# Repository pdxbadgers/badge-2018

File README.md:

# badge-2018  
BSidesPDX 2018 badge

## Art  
image resouce files

## FW  
C source code

## HW  
KiCad soruce files, BOM, datasheets

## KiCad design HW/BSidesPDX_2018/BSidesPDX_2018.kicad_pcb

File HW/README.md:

## Resources
passive compoenent footprints: https://github.com/esden/pretty-kicad-libs  
SAO symbol and footprint: https://hackaday.io/project/52950-defcon-26-shitty-add-ons
DigiKey symbols and footprints: https://www.digikey.com/en/resources/design-tools/kicad

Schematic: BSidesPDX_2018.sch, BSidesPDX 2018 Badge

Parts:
BT1: Battery_Cell; CR2030_Retainer
C1: 10u; C_0805
C2: 0.1u; C_0603
D1, D2, D3, D4, D5, D6, D7, D8, D9, D10, D11, D12: YLW_LED; OSRAM_LED
D13, D14: D_Zener; D_SOD-323
D101, D102, D103, D104: RGB_LED
J1: AVR-ISP-6; AVR_ISP_2x3_P2.54mm_SMD
J2: USB_B_Micro
R1, R2, R3, R4, R101, R102, R103, R104: 100R; C_0603
R5, R6: 68R; C_0603
R7: 1K5; C_0603
S1, S2: PTS645SM43SMTR92_LFS; Switch_Tactile_SMD_6x6mm_PTS645; MPN PTS645SM43SMTR92 LFS; Digi-Key_PN CKN9112CT-ND
U1: ATTINY861-15XD; TSSOP-20_4.4x6.5mm_P0.65mm
X1, X2, X3, X4: Badgelife_shitty_connector; PRESS_FIT_SAO_CNX

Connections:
/3V0: BT1.1, C1.1, C2.1, J1.2, J2.1, R7.1, U1.5 (VCC), U1.15 (AVCC), X1.1, X2.1, X3.1, X4.1
/B_PWM__D+: D101.4, D102.4, D103.4, D104.4, R5.1, U1.8 (XTAL2/PB5)
/D+: D13.1, J2.3, R5.2
/D-: D14.1, J2.2, R6.1, R7.2
/EN_RGB1: R101.1, U1.14 (PA4)
/EN_RGB2: R102.1, U1.13 (PA5)
/EN_RGB3: R103.1, U1.12 (PA6)
/EN_RGB4: R104.1, U1.11 (PA7)
/G_PWM: D101.3, D102.3, D103.3, D104.3, U1.4 (PB3)
/L_SWITCH_D-: R6.2, S1.1, S1.2, U1.7 (XTAL1/PB4)
/NC: J2.4
/ROW1: R1.1, U1.20 (PA0)
/ROW2: R2.1, U1.19 (PA1)
/ROW3: R3.1, U1.18 (PA2)
/ROW4: R4.1, U1.17 (AREF/PA3)
/ROW_1: D1.2, D2.2, D3.2, D4.1, D7.1, D8.1, R1.2
/ROW_2: D1.1, D4.2, D5.2, D6.2, D9.1, D10.1, R2.2
/ROW_3: D2.1, D5.1, D8.2, D10.2, D11.1, D12.2, R3.2
/ROW_4: D3.1, D6.1, D7.2, D9.2, D11.2, D12.1, R4.2
/R_PWM__MISO: D101.1, D102.1, D103.1, D104.1, J1.1, U1.2 (PB1)
/R_SWITCH: S2.1, S2.2, U1.9 (PB6)
/SCL_SCK: J1.3, U1.3 (PB2), X1.3, X2.3, X3.3, X4.3
/SDA_MOSI: J1.4, U1.1 (PB0), X1.4, X2.4, X3.4, X4.4
/~RESET: J1.5, U1.10 (~RESET~/PB7)
GND: BT1.2, C1.2, C2.2, D13.2, D14.2, J1.6, J2.5, J2.6, S1.3, S1.4, S2.3, S2.4, U1.6 (GND), U1.16 (AGND), X1.2, X2.2, X3.2, X4.2
unnamed: D101.2, R101.2
unnamed: D102.2, R102.2
unnamed: D103.2, R103.2
unnamed: D104.2, R104.2

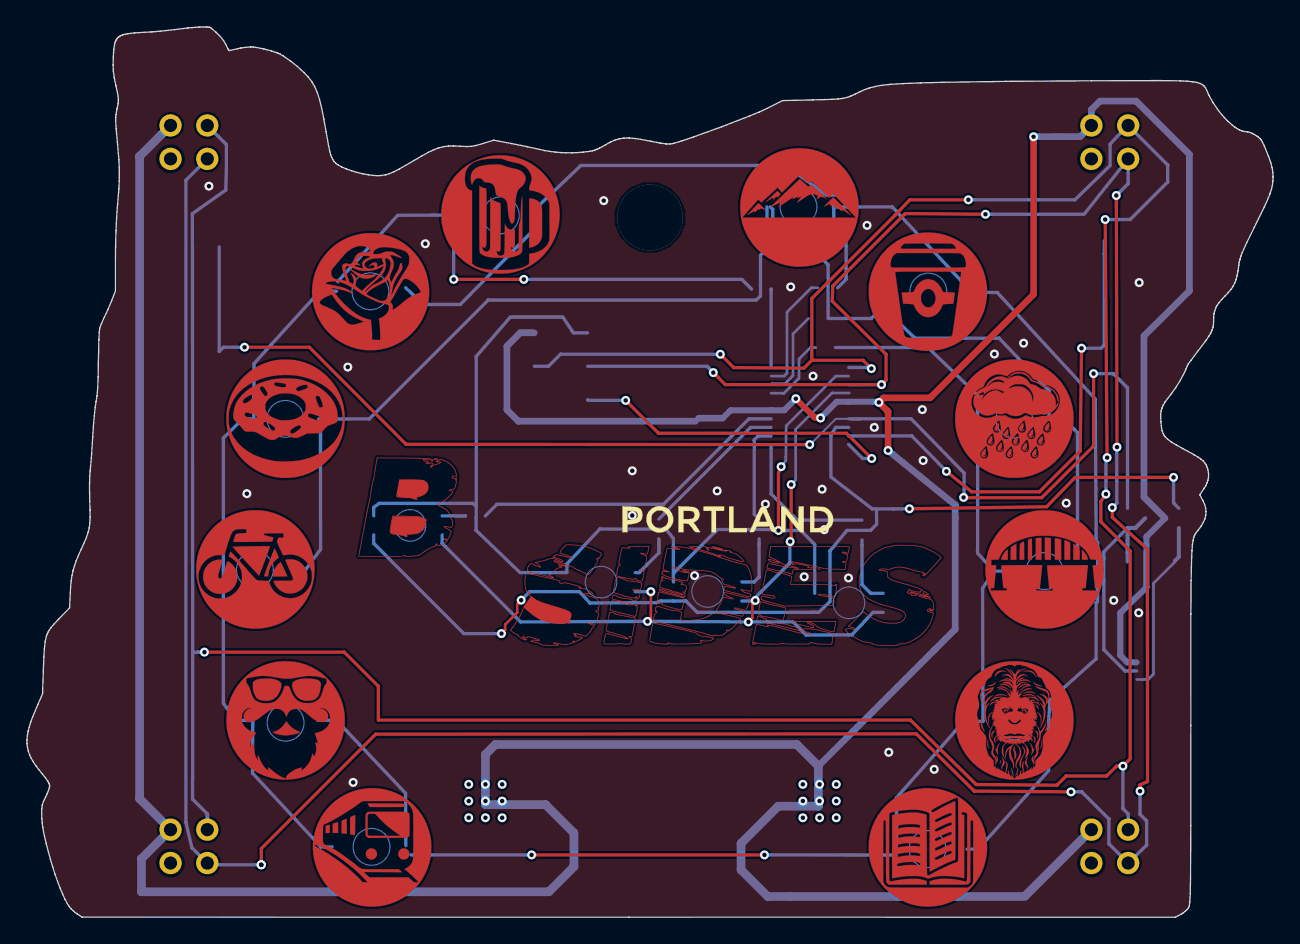
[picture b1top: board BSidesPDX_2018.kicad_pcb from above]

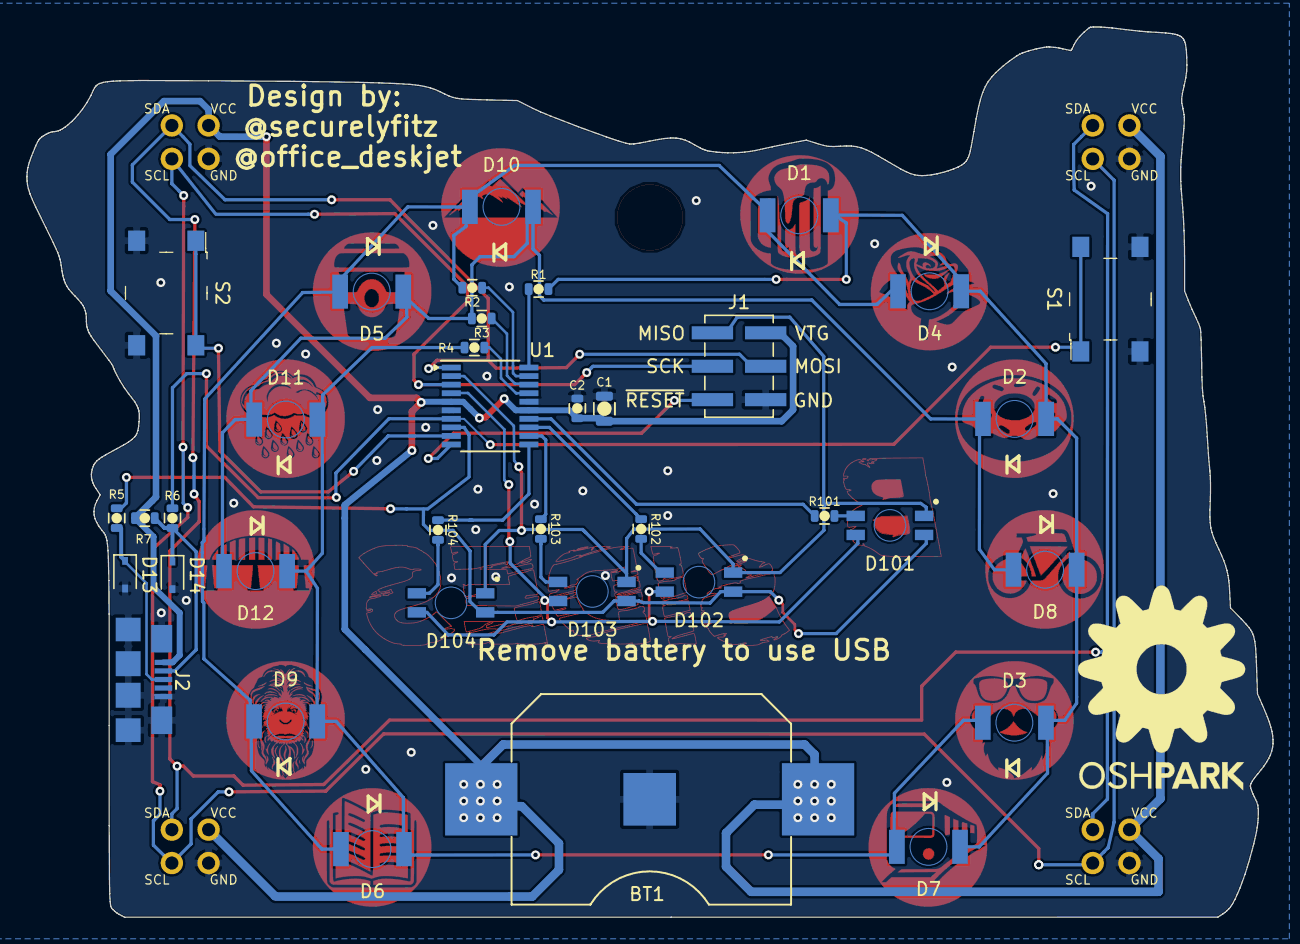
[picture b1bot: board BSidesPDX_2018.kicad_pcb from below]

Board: 2 copper layers, 94.7 x 67.7 mm, 44 parts (21 on the bottom side), 28 nets.

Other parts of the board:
ART_Cu: LOGO; F_Cu
MASK_ART: LOGO; F_Mask
PDX: LOGO; F_Silk

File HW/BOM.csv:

Description,Designator,Packing,Value,QTY/Board,Manufacturer Part #,Supplier Part #,Supplier Link,Comment,Packaging,Order Quantity,Order Cost
RGB LED,D101-D104,Gull Wing 4pin,RGB_LED,4,XZMDKCBDDG45S-9 ,1497-1257-2-ND,https://www.digikey.com/product-detail/en/sunled/XZMDKCBDDG4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,,Tape & Reel,2000,$859.18
Yellow LED,D1-D12,Gull Wing 2pin,YLW_LED,12,LY T776-S1T1-26-Z ,475-2801-2-ND ,https://www.digikey.com/product-detail/en/osram-opto-semicon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,,Tape & Reel,6000,$744.21
Zener Diodes,D13 D14,SOD323,D_Zener,2, MM3Z3V6T1G ,MM3Z3V6T1GOSDKR-ND ,https://www.digikey.com/product-detail/en/on-semiconductor/M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,,Digi-Reel,1000,$39.45
Resistors,R1-R4 R101-R104,SMD 0603,100R,8, CRGCQ0603J100R ,A130085TR-ND ,https://www.digikey.com/product-detail/en/te-connectivity-pa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,or similar replacement,Tape & Reel,5000,$12.64
Resistors,R5 R6,SMD 0603,68R,2,CR0603-JW-680ELF,CR0603-JW-680ELFTR-ND,https://www.digikey.com/product-detail/en/bourns-inc/CR0603-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,or similar replacement,Tape & Reel,5000,$9.41
Resistors,R7,SMD 0603,1K5,1, CRGCQ0603J1K5 ,A130092TR-ND,https://www.digikey.com/product-detail/en/te-connectivity-pa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,or similar replacement,Tape & Reel,5000,$12.64
Bypass Cap,C1,SMD 0805,10uF,1, CL21A106KPCLQNC , 1276-2402-6-ND ,https://www.digikey.com/product-detail/en/samsung-electro-me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,or similar replacement,Digi-Reel,500,$34.76
Bypass Cap,C2,SMD 0603,0.1uF,1,CL10F104ZB8NNNC,1276-1012-6-ND,https://www.digikey.com/product-detail/en/samsung-electro-me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,or similar replacement,Digi-Reel,500,$13.04
Battery Retainer,BT1,SMD 2pin,Battery_Cell,1,3034TR,36-3034TR-ND,https://www.digikey.com/product-detail/en/keystone-electroni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,,Tape & Reel,500,$156.75
MCU,U1,SOIC 20pin,ATTINY861-15XD ,1,ATTINY861A-XUR ,ATTINY861A-XURDKR-ND ,https://www.digikey.com/product-detail/en/microchip-technolo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,,Digi-Reel,500,$583.80
Switch,SW1 SW2,Gull Wing 4pin,PTS645SM43SMTR92_LFS,2,PTS645SM43SMTR92 LFS ,CKN9112TR-ND,https://www.digikey.com/product-detail/en/c-k/PTS645SM43SMTR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,,Tape & Reel,1000,$99.06
Connector,J2,SMD,USB_B_Micro,1,10118192-0001LF ,609-4613-6-ND ,https://www.digikey.com/product-detail/en/amphenol-fci/10118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,,Digi-Reel,500,$138.01
lanyard,N/A,N/A,N/A,1,N/A,N/A,TBD,,Bulk Bag,,
battery,N/A,CR2032,3V,1,N/A,N/A,ebay.com/itm/1000-X-CR2032-2032-DL2032-LM2032-BR2032-Ultra-Power-bulk-3V-lithium-battery-/222282215964,,Bulk Tray,,
,,,,,,,,,,,"$2,702.95"
,,,,,,,,,,,
MCU,U1,SOIC 20pin,ATTINY861-15XD ,1,ATTINY861-15XD,1611-ATTINY861-15XDCT-ND,https://www.digikey.com/product-detail/en/microchip-technolo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,We have this part as cut tape,cut tape,500,

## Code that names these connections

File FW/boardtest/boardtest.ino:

// ATtiny861 outputs
const int ROW1 = 0; // PA0
const int ROW2 = 1; // PA1
const int ROW3 = 2; // PA2
const int ROW4 = 14; // PA3

const int EN_RGB1 = 10; // PA4
const int EN_RGB2 = 11; // PA5
const int EN_RGB3 = 12; // PA6
const int EN_RGB4 = 13; // PA7
const int R_PWM = 8; // PB1
const int G_PWM = 6; // PB3
const int B_PWM = 4; // PB5

const int SAO_SDA = 9; // PB0
const int SAO_SCL = 7; // PB2

const int SPI_MOSI = 9; // PB0
const int SPI_MISO = 8; // PB1
const int SPI_SCK = 7; // PB2

const int DM = 5; // PB4
const int DP = 4; // PB5

const int L_SWITCH = 5; // PB4
const int R_SWITCH = 3; // PB6

const int RESET = 15; // PB7

void setup() {
  pinMode(EN_RGB1, OUTPUT);
  pinMode(EN_RGB2, OUTPUT);
  pinMode(EN_RGB3, OUTPUT);
  pinMode(EN_RGB4, OUTPUT);
  pinMode(R_PWM, OUTPUT);
  pinMode(G_PWM, OUTPUT);
  pinMode(B_PWM, OUTPUT);
  digitalWrite(EN_RGB1, 0);
  digitalWrite(EN_RGB2, 0);
  digitalWrite(EN_RGB3, 0);
  digitalWrite(EN_RGB4, 0);
  analogWrite(R_PWM, 255);
  analogWrite(G_PWM, 255);
  analogWrite(B_PWM, 255);

}

void configRows(int highrow,int lowrow,int z1,int z2)
{
  pinMode(z1,INPUT);
  pinMode(z2,INPUT);
  pinMode(highrow,OUTPUT);
  digitalWrite(highrow,1);
  pinMode(lowrow,OUTPUT);
  digitalWrite(lowrow,0);
}

void setLED(int ledNum)
{
  switch(ledNum){
    case 1: configRows(ROW4,ROW1,ROW2,ROW3);  break;
    case 2: configRows(ROW1,ROW4,ROW2,ROW3);  break;
    case 3: configRows(ROW3,ROW1,ROW2,ROW4);  break;
    case 4: configRows(ROW1,ROW3,ROW2,ROW4);  break;
    case 5: configRows(ROW2,ROW1,ROW3,ROW4);  break;
    case 6: configRows(ROW1,ROW2,ROW3,ROW4);  break;
    case 7: configRows(ROW3,ROW2,ROW1,ROW4);  break;
    case 8: configRows(ROW2,ROW3,ROW1,ROW4);  break;
    case 9: configRows(ROW4,ROW3,ROW1,ROW2);  break;
    case 10: configRows(ROW3,ROW4,ROW1,ROW2);  break;
    case 11: configRows(ROW4,ROW2,ROW1,ROW3);  break;
    case 12: configRows(ROW2,ROW4,ROW1,ROW3);  break;
    default:
      pinMode(ROW1,INPUT);
      pinMode(ROW2,INPUT);
      pinMode(ROW3,INPUT);
      pinMode(ROW4,INPUT);
  }
}

void RGBCycle(int delayVal=25)
{
  analogWrite(R_PWM, 255);
  analogWrite(G_PWM, 255);
  analogWrite(B_PWM, 255);
  for (int i=0; i <= 255; i++) {
    analogWrite(G_PWM, 255-i);
    delay(delayVal);
  }
  for (int i=0; i <= 255; i++) {
    analogWrite(G_PWM, i);
    analogWrite(B_PWM, 255-i);
    delay(delayVal);
    }
  for (int i=0; i <= 255; i++) {
    analogWrite(B_PWM, i);
    analogWrite(R_PWM, 255-i);
    delay(delayVal);
    }
  for (int i=0; i <= 255; i++) {
    analogWrite(R_PWM, i);
    delay(delayVal);
    }
  analogWrite(R_PWM, 255);
  analogWrite(G_PWM, 255);
  analogWrite(B_PWM, 255);
}

void cyclePWM()
{
    digitalWrite(R_PWM, 0);
    delay(1000);
    digitalWrite(R_PWM, 1);
    digitalWrite(G_PWM, 0);
    delay(1000);
    digitalWrite(G_PWM, 1);
    digitalWrite(B_PWM, 0);
    delay(1000);
    digitalWrite(B_PWM, 1);
}

void loop() {
  digitalWrite(EN_RGB1, 1);
  cyclePWM();  
  digitalWrite(EN_RGB1, 0);
  digitalWrite(EN_RGB2, 1);
  cyclePWM();  
  digitalWrite(EN_RGB2, 0);
  digitalWrite(EN_RGB3, 1);
  cyclePWM();  
  digitalWrite(EN_RGB3, 0);
  digitalWrite(EN_RGB4, 1);
  cyclePWM();  
  digitalWrite(EN_RGB4, 0);
     
  for (int i=1; i<=13; i++){
      setLED(i);
      delay(1000);
  }
  digitalWrite(EN_RGB1, 1);
  RGBCycle(10);    
  digitalWrite(EN_RGB1, 0);
  digitalWrite(EN_RGB2, 1);
  RGBCycle(10);    
  digitalWrite(EN_RGB2, 0);
  digitalWrite(EN_RGB3, 1);
  RGBCycle(10);    
  digitalWrite(EN_RGB3, 0);
  digitalWrite(EN_RGB4, 1);
  RGBCycle(10);   
  digitalWrite(EN_RGB4, 0);
}

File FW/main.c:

#define F_CPU 8000000UL

#include <util/delay.h>
#include <avr/io.h>

#define ROW_1 (1 << PA0)
#define ROW_2 (1 << PA1)
#define ROW_3 (1 << PA2)
#define ROW_4 (1 << PA3)


int main()
{
    DDRA = ROW_4 | ROW_3 | ROW_2 | ROW_1;

    //char LED[D0, D1, D2];

    for(;;) {
        PORTA |= (1 << PA2);
        _delay_ms(500);
        PORTA &= ~(1 << PA2);
        _delay_ms(500);
    }
}

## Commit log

2018-09-04 reloading everyting
2018-09-04 added SAO connector to local library. Added 5 SAO to schematic
2018-09-04 added SAO connectors, wires, and labels
2018-09-04 Added PWM busses and RGB LEDs
2018-09-04 Added resistor values. Added the first leg of CharliePlex LEDs
2018-09-04 added MCU datasheet, added charlieplex LEDs, and MCU to schematic
2018-09-04 adding datasheet
2018-09-04 lable RGB leds
2018-09-04 fixed wires on RGB, LED, MCU and caps.
2018-09-04 Fixed code directory. added ISP header, wired up PWM bussed
2018-09-04 adding files to match the previous commit
2018-09-04 wired up ISP header, SAO I2C, and PWM
2018-09-04 Wired, labeled, annotated charlieplex LEDs
2018-09-04 Building BOM, added switches
2018-09-04 Added more parts to BOM
2018-09-04 adding footprints
2018-09-04 Added a to do list.
2018-09-05 added Resistor and Capacitors to BOM
2018-09-05 Added batteries, LEDs and misc to BOM
2018-09-05 updating todo list
2018-09-05 added a README for hardwre, updated footprints
2018-09-05 Added LED and battery retainer datasheets. Added footprint for battery retainer. Update footprints in schematic.
2018-09-05 added press fit SAO connector, updated SAO footprints, added schematic for USB connecotr
2018-09-05 Corrected footprint for MCU. Updated USB parts
2018-09-05 removed USB connector, it will move to addon
2018-09-06 added foot print for programming header. Footpints are now assigned.
2018-09-06 working on art
2018-09-06 Adding SVG sources and links. fixing up board art
2018-09-06 update todo, vectorized coffe cup. renamed files
2018-09-06 fix up file book
2018-09-06 fix book?
2018-09-06 messing around with art more. Good state
2018-09-06 adding solder mask for art
2018-09-07 got the f.mask in place. working on icons
2018-09-07 Added At readme, more work done on art
2018-09-07 Art placed
2018-09-07 FRONT SIDE ART IS DONE
2018-09-07 adding generating kicad board art
2018-09-08 removed bottom SAO, Added USB back, updated library paths
2018-09-08 Removed temp art and mergered it into main project board.
2018-09-08 updated BOM, but missing resistor links. Updated Footprints
2018-09-09 Updated BOM USB connector, added USB footprint, updated ISP footprint, assigned footprints
2018-09-09 new netlist
2018-09-09 Layout work, added Datasheet for USB connector, fixed OSRAM_LED footprint, Fixed AVR ISP footprint.
2018-09-09 added OSHPark art, placed parts
2018-09-10 changed library settings, changed charliplexing circuit, fixed USB resistor
2018-09-10 Moved foot prints from libraries to locally.
2018-09-10 fixed avr isp orientation
2018-09-10 routed all leds, sao data lines. TO DO: 1. route power. i don't know how to change traces to larger lines in kicad 2. fix usb pins to connect to button pins instead. i still can't change schematic 3.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
2018-09-10 adding Joe's layout
2018-09-10 added zener diodes to USB data pins, changed wiring for USB data. PASS DRC
2018-09-10 power mostly routed, most signals routed
2018-09-10 layout done, FAILS DRC
2018-09-10 fixing drc issues
2018-09-10 fixing drc issues, now 40
2018-09-10 filled in lower B with copper, layout looks googd
2018-09-10 fixed up ground connections, Added bottom silks
2018-09-10 tying some vias through gnd to give physical attachmentwq
2018-09-11 Updated BOM, disconnected USB ID Pin
2018-09-11 finialized bom, but caps could change!
2018-09-11 exproted spreadsheet to CSV. Finialized BOM
2018-09-16 adding bootloader submodule
2018-09-17 adding detail to firmware readme, plus sample code
2018-09-17 readme formatting fixes
2018-09-17 updated TODO list
2018-09-17 cleaned up USB schematic, changed USB resistor values. fixed shorted traces around LED apature
2018-09-17 fixed the battery foot print and updated the layout. Thickened the VCC traces. moved the SDA_MISO and SLC_SCK traces to make room for thick VCC trace. export new netlist for chages to USB block. Ran 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
2018-09-17 marked pin 1 on U1. Updated ReadMe
2018-09-17 fixed OSH Park logo
2018-09-17 for some reason the YLW_LEDs got Silk on their pads. Removed silk from foot print and updated layout.
2018-09-18 Moved Art logo and ref labels to F.Fab layer. Added copper pours to F_Cu. removed some vias from pcb
2018-09-18 moved logo and ref to fab layer
2018-09-18 Move AVR ISP footprint to front layer, added copper around S, moved battery holder up a bit
2018-09-18 fixed ISCP header
2018-09-18 tried to fix art work, moved labels in Silk layer, updated layout
2018-09-19 BAD HACK: I edited the txt file of the LED footrpint, then updated all footprints in the schematic, then tweaked a few things. Someone competent should check this!
2018-09-19 fixed RGB_LED sik layer. Updated layout, fixed one trace on D10
2018-09-19 fix disconnected LED
2018-09-19 moved cap refs
2018-09-19 cleaned up traces to yellow LEDs. DRC passes. Visually checked no traces through led copper ring
2018-09-19 added gerbers
2018-09-19 adding gerbv project file for viewing
2018-09-19 redid ground pour. Updated USB Resistors in BOM
2018-09-27 blink light
2018-09-30 added led documentation, reading fuse bits
2018-10-04 LED blink code, delay time wrong
2018-10-18 Adding printout template, paper art
2018-10-18 finished front of paper badge layout
2018-10-21 Added Fuse programming to Makefile to set clock to 8Mhz
2018-10-22 added test code for RGB PWM, looks like LEDs are wired wrong
2018-10-23 RGB PWM test code
2018-10-23 code working for Red channel
2018-10-23 moved code to avr libc
2018-10-23 code clean up
2018-10-23 G and B are wrong in foot print. Need to fix in FW
2018-10-23 The finished paper badge and resources
2018-10-24 converting arduino code to avr-libc
2018-10-24 more converting, no testing
2018-10-24 compiles without error, no runtime testing
2018-10-24 charleplex code works correctlygit status
2018-10-24 make flash now builds before flashing
2018-10-24 Making an RGB LED test project, not PWM!
2018-10-24 working on RGB LED test code
2018-10-24 got the correct mapping for PWM pins
2018-10-24 RBG LED test code works correctly
2018-10-24 understanding the PWM registers
2018-10-24 red pwm ok
2018-10-24 git ignore bin files
2018-10-24 clean code in RGB_LED_test
2018-10-24 got the pins right for PWM
2018-10-24 RBG PWM working, doing all colors one LED at a time
2018-10-24 RGB PWM code done. Cycles R, G, B per each LED
2018-10-24 added test code for implementing the RGB PWM via a timer ISR. copied coder from RGB PWM test
2018-10-24 init functions for timers
2018-10-24 more init functions, moving code
2018-10-24 fixing up timer init to 125Khz
2018-10-24 changed time0 to 12.5 Khz
2018-10-24 pin toggles in for loop, but at 360Khz, code in ISR not running
2018-10-24 timer0 configured correctly, loop code works, no test on ISR
2018-10-24 time frequency correct, but ISR not happening
2018-10-24 fixed typo for enabling interrupt timer0, works now
2018-10-24 got the ISR working. Gave up on having two ISR for A and B. Implemented a software timer using OCR0A
2018-10-24 moved old code into temp
2018-10-24 PWM one led all colors via timer ISR works
2018-10-24 All RGB Leds now work on timer/ISR. had to change the timer frequency to get rid of delay in lighting the 103 104 LEDS.
2018-10-24 new project, combine led code together
2018-10-24 combining all the led code into all_leds.c
2018-10-24 cleaned up code, compiles and works
2018-10-24 adding code for yellow led speed chnaing with button R_SWITCH
2018-10-24 button press plays well with rgb leds
2018-10-24 getting random yellow led blink
2018-10-25 Yellow LED patter works with button. Button debounce is horrible.
2018-10-25 tried different timming for button, still bad debounce.
2018-10-25 change makefile to use USBASP programmer
2018-10-25 GOLDEN IMAGE
2018-10-26 add some info about flashing over USB
2018-10-26 fix MD
2018-10-30 disabling RGB LEDs
